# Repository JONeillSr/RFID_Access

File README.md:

# RFID Access Control

A door-access controller for ESP32 boards. Tap an enrolled RFID card to release a
door strike; everything else is denied. Built around a small set of reusable
libraries (WiFi provisioning, OLED display, splash screen) so the same codebase
drops onto multiple doors and multiple ESP32 variants with only a build-flag
change.

Status indication is on-device and over the network: a 0.96" OLED shows the
current state, an RGB LED gives an at-a-glance verdict, an active buzzer gives
audible feedback, and a built-in web server exposes status and over-the-air
firmware updates.

---

## Features

- **RFID access control** — Paxton P-series proximity reader (Clock & Data or
  Wiegand), enrolled-card allow-list stored in NVS (survives reboot and
  reflash). The reader can be mounted up to 100 m from the controller.
- **Door-side feedback** — drives the reader's own red/amber/green LED lines:
  amber "ready" when idle, green on grant, red on deny.
- **Fail-secure relay** — drives a door strike through a relay; the strike is
  de-energised (locked) whenever the controller is off or unpowered.
- **Exit button** — request-to-exit input (push-to-make to GND) releases the
  door from the secure side, no fob needed.
- **Door contact** — an optional magnetic contact on the frame reports a door
  **forced** open (opened with no grant, exit press or unlock window) or **held
  open** too long. Off until switched on, from the admin app or `/setup`. DevKit
  and S3 only; the C6 and C3 have no free input. *Bench-proven 2026-09-19 with a
  jumper standing in for the contact; not yet run with a reed switch fitted.*
- **Unlock schedule** — optionally holds the door unlocked during a configured
  time window on selected days (e.g. 08:00–17:00 weekdays), set from the web
  UI and stored in NVS. Time comes from NTP and the schedule **fails secure**:
  no time sync means the door stays locked.
- **Non-blocking throughout** — no `delay()` in the running system; relay
  release, result-screen revert, and LED timing all run off deadlines checked in
  `loop()`. FreeRTOS tasks separate RFID polling, access processing, and the web
  server.
- **OLED status display** — splash screen on boot, then an idle screen showing
  the mDNS hostname, IP address, and OTA hint; GRANTED / DENIED verdicts on tap.
- **Panel status LED** — green while the door is unlocked (plus red on denied,
  on boards with a free red channel; the C6's went to the exit button). Primary
  grant/deny indication is at the door, on the reader's own LEDs. Note the P50
  also beeps by itself on every token read and holds its amber LED as a
  power/ready indicator — both are built into the reader.
- **WiFi provisioning** — first boot raises a captive-portal AP with a network
  scanner; credentials are stored and reused on subsequent boots.
- **Changing WiFi without a site visit** — `/setup` moves a door to another
  network and **returns it to the working one if the new network does not come
  up**. For a network the door cannot see from where it is, the admin app arms
  the setup AP for its next restart, or holding the exit button at power-on
  opens the portal with no network at all.
- **mDNS** — reachable at `http://<hostname>.local` once connected.
- **Per-door identity** — one firmware image for every door. Each board derives a
  unique device ID from its MAC, so units never collide on the network, and
  hostname / door name / site name are set per unit on `/setup`.
- **OTA updates** — firmware can be flashed over the network via ElegantOTA at
  `/update`, or published once to the backend, which offers it to every paired
  door on that board running an **older** version. Going back is an explicit
  `--rollback`, never an accident of publishing.
- **Remote release** — an Operator can unlock a door for one relay hold from the
  admin app (**Doors → Release**), for letting in someone without a fob. Lands
  within seconds, is logged as *released remotely by &lt;name&gt;*, and is ignored if
  it reaches the door more than a minute late. Firmware 2.10.0 and later.
- **Remote restart** — an Admin can restart a door from the admin app
  (**Doors → Restart**). It waits until the strike is not mid-release, and lapses
  if the door does not check in within 15 minutes. Firmware 2.9.0 and later.
- **Remote logging** — live device log over the network at `/webserial` and via
  a telnet console (port 23), showing boot diagnostics and access events with no
  USB cable needed.
- **Multi-board** — one codebase targets the XIAO ESP32-C6, ESP32-C3, ESP32-S3,
  and the classic ESP32 DevKit, selected by a single build flag.

---

## Hardware

### Bill of materials

| Part | Notes |
|------|-------|
| ESP32 board | XIAO ESP32-C6 (primary), or ESP32-C3 / ESP32-S3 / classic ESP32 DevKit |
| Paxton reader | P-series 125 kHz proximity, e.g. P50 / 345-110-US; Clock & Data output |
| Pull-up resistors | 2× 10K, Data and Clock lines to a **clean 3.3 V rail** (not the ESP32's 3V3 pin — see wiring) |
| Exit button | any normally-open momentary switch (e.g. 30 mm arcade button) |
| Door contact *(optional)* | magnetic reed contact, **closed when the door is shut** |
| SSD1306 OLED | 0.96", I²C, address `0x3C` |
| Relay module | e.g. SONGLE SRD-05VDC-SL-C, active-LOW input with onboard driver + coil flyback diode |
| Door strike | DC, fail-secure (e.g. RCI L65) |
| Flyback diode | 1N4007 across the door strike — **required**, see Troubleshooting |
| RGB LED | common-cathode, with a current-limiting resistor per channel (220–330 Ω) |
| Active buzzer | |
| Power | 12 V supply; buck converters to 5 V and 3.3 V |

### Pin assignments

Pins are defined per board in `src/Pins.h`, with board-identity facts (I²C
defaults, capability flags, strapping-pin warnings) in `lib/BoardConfig/BoardConfig.h`.
Application code never references a raw GPIO — only the `PIN_*` names — so
retargeting a board is purely a build-environment change.

> **Verification status.** The **XIAO ESP32-C6** map is fully bench-verified
> in a working build: relay fail-secure confirmed clean through reboot with a
> meter, and Paxton P50 reads confirmed end-to-end (Clock & Data decode with
> LRC validation, reader LED control, exit button). The **classic ESP32
> DevKit** relay/buzzer/OLED/RGB pins are bench-verified from the RC522-era
> build; its Paxton pins reuse GPIOs proven there but haven't carried reader
> traffic yet. The **C3** and **S3** maps are plausible, strapping-pin-safe
> defaults that have **not** been hardware-verified. Before deploying to a C3
> or S3, confirm the relay pin shows no spurious pulse at boot (see
> Troubleshooting → "Verify the relay pin at boot"). Adjust `src/Pins.h` as
> needed.

**XIAO ESP32-C6:**

| Function | GPIO |
|----------|------|
| Paxton Data/D0 | D8 |
| Paxton Clock/D1 | D9 |
| Paxton Red / Green / Amber LED | D3 / D10 / D0 |
| Buzzer | D2 |
| Relay IN | GPIO1 |
| OLED SDA / SCL | 22 / 23 |
| Exit button | D6 (to GND) |
| Panel LED G | D7 (lights while door unlocked) |
| Panel LED R / B | not assigned — D6 was repurposed for the exit button; the reader's red LED shows "denied" at the door |

On the C6 every pad is now in use, so the panel LED is reduced to its green
channel only (dark idle, green while the door is unlocked). Full at-the-door
feedback — amber ready, green granted, red denied — comes from the Paxton
reader's own LEDs.

**Classic ESP32 DevKit:**

| Function | GPIO |
|----------|------|
| Paxton Data/D0 | 19 |
| Paxton Clock/D1 | 18 |
| Paxton Red / Green / Amber LED | 17 / 23 / 4 |
| Buzzer | 13 |
| Relay IN | 14 |
| OLED SDA / SCL | 21 / 22 |
| Exit button | 32 (to GND) |
| Door contact | 33 (to GND) |
| LED R / G / B | 25 / 26 / 27 |

### Paxton reader wiring

The reader connects with the same terminal roles as on a Paxton Net2 ACU —
if migrating from a Net2, each reader wire moves from the Net2 reader-port
terminal to the matching ESP32 connection.

Paxton P50 (345-110-US) wire colors — bench-verified on this unit by
grounding the LED lines and watching the data lines during a tap. Note the
loom differs from older Paxton manuals (no brown wire; Red LED is purple
here, not brown):

| Wire color | Function | Connection (XIAO C6) |
|-----------|----------|----------------------|
| Red | 12V | PSU + |
| Black | 0V | PSU − / ESP32 GND (plus cable screen) |
| Yellow | Data/D0 | D8 (10K pull-up to 3V3) |
| Blue | Clock/D1 | D9 (10K pull-up to 3V3) |
| Purple | Red LED | D3 |
| Orange | Amber LED | D0 |
| Green | Green LED | D10 |
| White | Media detect (reader output; unconfirmed) | not connected |

Yellow/blue both carry the transmission, so a meter can't tell Data from
Clock — wire as above and tap a token: card numbers reading correctly
confirms it, while a rising decode-error counter on `/status` with no reads
means the pair is swapped (swap the two wires and retest).

> **Warning:** Paxton colors do NOT follow the common Wiegand convention.
> On most third-party readers green = D0 and white = D1; on a Paxton, green
> is an LED line — the data pair is **yellow and blue**. Grounding an LED
> wire lights that LED; the data/clock wires blip low during a card read.

- **12V / 0V** — from the 12 V supply. The reader's 0V must be commoned with
  the ESP32's ground, or the data lines have no reference.
- **Data/D0 and Clock/D1** — open-collector outputs from the reader. Fit a
  **10K pull-up from each line to a clean 3.3 V source** (never to 5 V or
  12 V — ESP32 pins are not 5 V tolerant). Verify with a meter that both lines
  idle at ~3.3 V before connecting to the GPIOs.

  > **Use a stiff 3.3 V rail for the pull-ups, not the ESP32 module's own
  > 3V3 pin.** Bench-proven the hard way: pull-ups referenced to the ESP32's
  > 3V3 pin produced randomly duplicated clock bits (the module's rail
  > bounces with WiFi transmit bursts, so slow rising edges re-cross the
  > input threshold). Moving the pull-ups to a dedicated 3.3 V buck output
  > fixed it completely. The pull-up rail must share ground with the ESP32,
  > power up/down with it, and measure ≤ ~3.5 V.
- **Red / Amber / Green LED** — active-low control inputs; the firmware drives
  them open-drain (sinks to light, floats to release), the same way the Net2
  does. Measure each LED line's idle voltage first: if one floats above
  3.3 V, sink it through a small NPN transistor or N-MOSFET instead of the
  GPIO directly.
- **Media Detect** — unused; leave disconnected.

Cable: Cat5 or Belden 8723 class, up to **100 m**. Past 25 m, double up the
12V and 0V cores to limit voltage drop (Paxton's own guidance for Net2 runs).

### Exit button, door contact and unlock schedule

**Exit button:** any push-to-make button wired between `PIN_EXIT_BTN` and
GND (internal pull-up; active low). Pressing it releases the door for the
normal relay hold time — no fob required. Wiring is identical to the Net2's
Exit/0V terminal pair.

**Door contact** *(new in 2.8.0)*: a magnetic reed contact on the frame,
wired between `PIN_DOOR_CONTACT` and GND (internal pull-up) — GPIO 33 on the
DevKit, 17 on the S3. The C6 and C3 have no free input. Then switch it on: for a
paired door, in the admin app under **Doors → edit → Door contact fitted**
(`/setup` shows it read-only there, as it does the reader format); otherwise on
the door's own `/setup`. It is off by default because an unwired
input reads as an open door.

- Use a contact that is **closed when the door is shut**. A cut wire then reads
  as open and raises an alert, instead of reading "closed" forever. (For the
  other kind, set `DOOR_CONTACT_OPEN_LEVEL` to `LOW` in `src/Pins.h`.)
- **Door forced** is reported when the door opens with no grant or exit press in
  the last relay hold plus 2 s, and no unlock window open.
- **Door held open** is reported when it stays open longer than the limit on
  `/setup` (default 60 s) after the last release ended, and again with the total
  time once it closes.
- **If the door opens from inside without the exit button** (a lever handle),
  every such exit reads as forced. Wire a request-to-exit switch or motion
  sensor to the exit button input before relying on the forced alert.
- Forced openings appear on the admin dashboard. See Phase 6 in `ROADMAP.md`
  for what is verified so far.

**Unlock schedule:** configured on the `/config` page — enable, start/end
time, and days of week; an end time before the start time makes an overnight
window. While active, the relay is held energised, the reader LED shows
green, and the OLED idle screen reads `** DOOR UNLOCKED **`. The clock comes
from NTP (synced on WiFi connect; timezone is `TZ_INFO` in `src/main.cpp`,
default US Eastern). Fail-secure rule: if the clock has never synced since
boot, the schedule stays inactive and the door stays locked. Note that a
fail-secure strike is energised for the whole window — check your strike's
duty-cycle rating, or use a maglock/continuous-duty strike for long windows.

The reader outputs **Clock & Data** (Paxton's native format) by default, which
is what the firmware expects. If the reader has been switched to Wiegand with a
Paxton configuration card — or a third-party Wiegand reader is fitted — set
**Reader format → Wiegand** and **reboot**. Set it in the **admin app** (Doors →
edit → Reader format) for a paired door; `/setup` shows it read-only there, the
same as the roster and schedule. An unpaired door sets it on `/setup` (the format decides which
interrupts attach, so it is applied at boot; `/setup` shows "reboot pending"
until then, and `/status` shows the running format). Wiegand D0 goes to the
Data terminal and D1 to the Clock terminal. Only Paxton on Clock & Data is
verified so far — qualify any other reader with
[`docs/reader-qualification.md`](docs/reader-qualification.md) before promising it.

### Relay and door-strike wiring

The relay switches +12 V to the door strike's positive terminal (high-side
switching); the strike's other lead returns to ground. **A 1N4007 flyback diode
must be fitted directly across the door strike's two terminals**, banded end
(cathode) toward the strike's positive (relay-NO) lead. Without it, the strike's
inductive kick on relay release couples into the shared supply and can wedge the
RFID reader. The relay module's own onboard diode protects only the relay coil,
not the strike — see Troubleshooting for the full story.

---

## Software setup

### Prerequisites

- [PlatformIO](https://platformio.org/) (VS Code extension or CLI)
- The **pioarduino** fork of the ESP32 platform — required for current
  ESP32-C6 support. This is pinned in `platformio.ini`, so PlatformIO fetches it
  automatically; no manual install needed.
- Python, for the tools in `tools/` and for the git hooks below.

### Enable the git hooks (once per clone)

```bash
git config core.hooksPath .githooks
```

Git does not use tracked hooks until you point it at them, and nothing warns you
— so a fresh clone silently has no protection until this is run.

The hooks refuse to commit anything that looks like a **card number**, in file
content and in commit messages alike. Fob numbers are credentials: anyone holding
one can clone a working card. The `.gitignore` rules already keep `seed.json` and
`*-fobs.json` out, but they protect known *files* — a number pasted into source
as a placeholder walks straight past them, which is exactly how one reached a
commit here. Run `python tools/check_card_numbers.py --all` to scan the whole
tree by hand.

### Build environments

Each board has its own environment in `platformio.ini`. The default is the C6.

| Environment | Board | Build flag |
|-------------|-------|------------|
| `seeed_xiao_esp32c6` | XIAO ESP32-C6 (default) | `BOARD_XIAO_ESP32C6` |
| `esp32c3` | ESP32-C3 DevKitM | `BOARD_ESP32C3` |
| `esp32s3` | ESP32-S3 DevKitC | `BOARD_ESP32S3` |
| `esp32dev` | classic ESP32 (WROOM) | `BOARD_ESP32DEV` |

All environments use the `min_spiffs` partition scheme to keep two OTA app slots
on 4 MB flash. ElegantOTA is forced into sync-WebServer mode via
`-D ELEGANTOTA_USE_ASYNC_WEBSERVER=0`.

### Build and flash

Build for the default board (C6):

```
pio run
```

Build for a specific board:

```
pio run -e esp32dev
```

Flash over USB:

```
pio run -e seeed_xiao_esp32c6 -t upload
```

Serial monitor (115200 baud):

```
pio device monitor
```

> **Note on the ESP32-C6 and serial:** the C6 uses native USB CDC, which drops on
> reboot and re-enumerates too slowly to catch boot messages. Diagnostics on the
> C6 therefore go to the OLED and the web `/status` page, not the serial monitor.
> The classic ESP32 DevKit uses an external USB-UART chip whose serial **survives
> reboot**, so on that board the monitor is fully usable for boot debugging.

---

## First-time use

1. **Flash** the firmware for your board.
2. **Provision WiFi.** On first boot (no stored credentials), the device raises a
   WiFi access point named `RFID-Setup`. Join it from a phone or laptop; a
   captive portal opens automatically (or browse to `http://192.168.4.1`). Pick
   your network, enter the password, and save. The device reboots and connects.

   The same portal appears if the door boots while its saved network is down —
   after a power cut, for example. **It does not need re-entering:** from 2.7.4
   the door keeps retrying the saved network and returns on its own within a
   couple of minutes of the network coming back. Earlier firmware stayed in the portal
   until someone rejoined it.
3. **Find the device.** Once connected, the OLED shows the hostname, the IP
   address, and the OTA hint. Out of the box the hostname is this board's unique
   device ID (`rfid-a1b2c3.local`) — read it off the OLED and browse to it, or
   use the IP. Give it a friendlier name on `/setup`.
4. **Enrol cards** via the web interface, then tap to test: a granted card
   energises the relay (green LED, door unlocks); an unknown card is denied (red
   LED).

### Web endpoints and remote logging

The web server, OTA, status page, and remote log are owned by the reusable
`WebService` module (`lib/WebService/`), which creates the server, serves the
common admin pages, and lets the project register its own routes and inject
app-specific status fields.

| Path | Purpose |
|------|---------|
| `/` | main web UI (card enrolment) |
| `/config` | fob management + unlock-schedule configuration |
| `/setup` | device settings: splash hold, mDNS hostname, door name, site name, **WiFi network** (try-then-revert), **reader format**, **relay hold and result-screen hold**, door contact and held-open limit, **backend host**, cloud pairing code; plus a **Reboot device** button |
| `/api/schedule` | GET current schedule/state, POST to update |
| `/api/add` `/api/rename` `/api/remove` | fob management (POST, JSON) |
| `/api/list` `/api/taps` | roster and recent taps (GET, JSON) |
| `/status` | live status page: device ID, door and site, WiFi IP, **`Signal:`** strength in dBm with a rating, channel and access point (BSSID), mDNS name, uptime, **heap** (free / min since boot / largest block), OLED, **`Reader:`** running line format (and any pending change), time **and how long since NTP**, schedule, **`Relay:`** hold per grant and result-screen hold, **`Contact:`** door state, **`WiFi:`** network and any move in progress, enrolled count, **`Backend:`** host, cloud sync state, **`Retry:`** backoff when not on the normal poll, **`Remote:`** how a remote release will arrive (polling the feed every 3 s, or next sync only and why), event spool, last tap |

The heap line is worth reading properly, because two of its three numbers have
already been the difference between a diagnosis and a guess:

```
Heap:  132 KB free, min 71 KB since boot, largest block 91 KB
```

**Free heap is the least useful of the three.** It describes the instant you
looked. `min since boot` survives a spike that has passed, and `largest block` is
what large allocations actually compete for — a TLS handshake needs ~45 KB
*contiguous*, so plenty free in small pieces will still fail. A roster-write
failure was once diagnosed from exactly this line while free heap looked
entirely healthy.

From 2.12.3 a note under the line says when the **release feed** connection is
open and roughly how much it holds (about 55 KB). The feed keeps a TLS session
open between syncs to check for remote releases every 3 seconds, and closes it
before each sync, so a reading taken while it is open understates what a sync
gets. Fragmentation shows as a small largest block with the feed **closed**. The
copy the admin app shows (**Doors → Status**) is taken during a sync, with the
feed closed, so it is the one to judge by.

#### Write endpoints go read-only once a door is paired

`/api/add`, `/api/rename`, `/api/remove` and `POST /api/schedule` answer **409**
while a door is centrally managed, and `/config` shows a banner saying so. The
read endpoints are untouched, so a door still explains itself locally even with
the network gone.

A controller that can enrol its own fobs while offline is an attack surface:
anyone reaching one door's page could add themselves, and the central database
would not know until it silently overwrote the entry on the next sync. It also
leaves the roster with exactly one writer, so local and central cannot drift.

The accepted cost is that a fob cannot be enrolled during a WAN outage — doors
keep working from their cached rosters, but the fob list is frozen until the link
returns. **Unpaired units keep full local control**, so a bench unit behaves
exactly as it always did, and unpairing on `/setup` hands control back
immediately without a reboot.

#### The backend is runtime configuration

The host a door reports to is stored in NVS and set on `/setup`, not compiled in.
`CLOUD_HOST_DEFAULT` in `src/main.cpp` is only the value a door uses until told
otherwise, so existing units need no migration.

One image therefore serves every deployment. **Changing the host unpairs the
door** — a device key is issued by the backend that minted it and is meaningless
to another — so enter a pairing code from the new backend in the same submission.
The host is applied first precisely so that works in one step.
| `/footer.js` | shared footer the WebService module injects into every page |
| `/update` | ElegantOTA firmware upload |
| `/webserial` | live device log (self-refreshing); shows boot diagnostics and access events |

A **telnet log console** is also available on port 23 (`telnet <host>.local`),
showing the same log stream as `/webserial`. Both are fed by `webService.log()`
calls placed at key events (reader-interface boot line, WiFi connect, each
access grant or deny). Note the telnet console is plaintext and unauthenticated — fine for a
trusted LAN or bench, but consider disabling it on field units exposed to
untrusted networks.

### Per-door deployment

**One firmware image serves every door.** Identity comes from hardware and NVS,
not from a build flag, so nothing needs recompiling per unit.

Each board derives a permanent **device ID** from its MAC — `rfid-a1b2c3` — which
is unique out of the box, survives reflashing and an NVS erase, and is what a
backend keys on. Until you set a hostname, that device ID *is* the mDNS name, so
**two units can never collide on the network by default**.

On `/setup` you can give each unit friendlier labels:

| Field | Purpose |
|-------|---------|
| mDNS hostname | Network name, e.g. `rfid-front` → `http://rfid-front.local` |
| Door name | Human label for reports, e.g. "Front Door" |
| Site name | Groups doors sharing a building, e.g. "Main Shop" |
| Device ID | Read-only; the fixed MAC-derived identity |

Door and site names apply immediately. A changed **hostname takes effect after a
reboot**, since the mDNS responder is started at boot — and `/setup` carries a
**Reboot device** button for exactly that, so renaming a door doesn't mean walking
to it. The reboot endpoint is POST-only, so no link prefetch or crawler can
restart a unit. The lock is fail-secure, so a reboot leaves the door locked.

Hostnames are sanitised before use — lowercased, restricted to `a-z0-9-`, spaces
and underscores folded to `-`. Typing "Front Door" yields `front-door` rather than
an invalid label that would make the unit silently unresolvable.

Identity flows from `DeviceIdentity` into `wifiMgr.setHostname()`, the OLED idle
screen, and the `/status` page, which now leads with device ID, door, and site so
you can tell units apart at a glance.

---

## Project structure

```
lib/                    reusable, application-agnostic libraries
  BoardConfig/          per-board identity + capability flags (compile-time)
  Display/              SSD1306 OLED helpers (caller owns the I2C bus)
  SplashScreen/         boot splash
  WiFiManager/          provisioning, STA lifecycle, mDNS, NTP time sync
  WebService/           owns the web server: /status, /update (OTA),
                        /webserial, telnet log console, shared page footer,
                        optional /setup; projects add routes
  DeviceSettings/       NVS settings store (WebService dependency)
  DeviceIdentity/       MAC-derived device ID, mDNS hostname, door/site labels
  Roster/               LittleFS credential store: hash-keyed, CRC-checked,
                        atomic save, atomic wholesale replace for cloud sync
  EventLog/             durable append-only event spool held until the backend
                        acknowledges it (taps, exit, schedule, boot, config,
                        firmware, door forced/held)
  DoorContact/          forced-open and held-open decisions from a reed contact.
                        Pure logic: the caller reads the pin and supplies the
                        release state, so the rules sit in one readable place
  CloudSync/            backend sync client + OTA: uploads spooled events,
                        applies the roster/config the server returns, and takes
                        firmware updates. Runs on its own task and is NEVER in
                        the access decision path. Embeds its own TLS trust
                        anchors (certs/ + RootCerts.h) -- an ESP32 has no system
                        trust store.
  AccessControl/        access decision + recent-tap log (storage lives in Roster)
  Events/               app event types + queue (card-tap, exit-request)
  PaxtonReader/         Clock & Data / Wiegand reader driver + reader LEDs
  UnlockSchedule/       NVS-backed timed-unlock window (fails secure w/o NTP)
  WebHandlers/          project-specific web UI routes
src/                    project-specific code
  main.cpp              wiring, tasks, screens, relay/LED/buzzer logic
  Pins.h                per-board peripheral pin map
  JTLogoBitmap.h        splash bitmap
tools/                  operational scripts
  backup-doors.ps1      snapshot a door's fobs + schedule before a reflash
  check_partitions.py   validate partitions_rfid.csv (incl. NVS preservation)
  check_roster_logic.py exercise Roster's ordering/lookup algorithms
  gen_certs.py          regenerate lib/CloudSync/RootCerts.h from the PEMs in
                        lib/CloudSync/certs/ (see that header for how to
                        re-extract and verify an anchor before trusting it)
  wrap_standalone.py    regenerate docs/board-bringup.html from the published
                        version (adds the doctype/head a hosted page supplies)
docs/                   printable references
  board-bringup.html    one-page field guide for adding a new board type: the
                        gates, the verification at each one, and where mistakes
                        stop being recoverable. Open it directly and print.
cloud/                  Azure backend (TypeScript, deployed separately)
  shared/types.ts       contract shared by the API and the admin web app
  api/                  Azure Functions: device sync/enroll + the admin API
  web/                  admin web app (Preact + Vite) on Static Web Apps
  infra/                Bicep: storage, tables, Function App, SWA, observability
```

Each of those three has its own README covering deployment and the decisions
behind it; the admin app is live at `https://access.jtcustomtrailers.com`.

`ROADMAP.md` tracks the multi-door / cloud programme: what is built, what is
next, and — more usefully — why each decision went the way it did.

The split is deliberate: `lib/` holds code reusable across projects and visible
to other libraries; `src/` holds this project's specifics. Two complementary
networking modules divide the work cleanly: **WiFiManager** owns *connectivity*
(provisioning, STA lifecycle, reconnect, mDNS), while **WebService** owns the
*web/admin surface* (the long-lived server, OTA, status, remote logging).
Neither reaches into the other; a project composes both.

---

## Design principles

- **Non-blocking only.** `delay()` is forbidden in the running system; all timing
  uses deadlines checked in `loop()` or `vTaskDelay` inside tasks.
- **Canonical storage, convert at the edges.** State is stored in base units and
  formatted only at the display/input boundary.
- **Modular and board-agnostic.** Reusable modules in `lib/`, project specifics in
  `src/`, board differences behind a single build flag.
- **Fail-secure.** The lock defaults to secured; the relay is brought to a safe
  state before anything else at boot.

---

## Troubleshooting

### Granted tap locks up the reader (no further cards read until power-cycle)

**Cause:** inductive flyback. On a granted tap the relay energises the door
strike; when the relay releases, the strike's collapsing magnetic field produces
a voltage spike. On a shared supply that spike couples into the RFID reader and
wedges it. The tell is that the lockup happens on relay **release**, and only on
granted taps (denied taps never fire the relay).

**Fix:** fit a 1N4007 flyback diode **directly across the door strike's two
terminals**, banded end (cathode) toward the strike's positive (relay-NO) lead.
Mount it at the strike, not back at the board, so the spike is clamped at its
source. The relay module's onboard diode only protects the relay coil — the
external strike is a separate inductor and needs its own clamp.

This applies to **DC** strikes. An AC strike needs an RC snubber or MOV instead;
a diode across an AC coil will conduct every half-cycle and fail.

### Reading the reader counters on /status

`Reader: Paxton Clock&Data, E edge(s), N error(s), R repaired` is a built-in
diagnostic ladder (a tap should add ~80-100 edges):

- **Edges don't move on a tap** → no signal reaches the GPIOs at all. The
  reader beeping proves nothing — its sounder fires on every read, powered or
  not by your wiring. Check, in order: reader 0V **commoned with the ESP32
  ground** (without a shared reference the open-collector lines never swing);
  the pull-ups (both lines should idle at ~3.3 V at the ESP32); the wires on
  the right pads. Tip: the exit button test — press it and watch for the
  reader's green LED — proves ground + LED drive in one shot.
- **Edges jump, errors increment, never a card number** → bits arrive but
  won't parse. Every failed frame is logged with its raw bits
  (`[paxton] undecodable frame: 0001101...` at `/webserial`), which makes
  the cause readable: wrong line format (reader switched to Wiegand → set
  **Reader format** on `/setup` and reboot), swapped Data/Clock, or all-same
  bits (the data pin is on the wrong wire — Media Detect also dips during a
  read and fools a multimeter).
- **Reads work but `repaired` keeps climbing** → line quality is marginal.
  The driver absorbs one duplicated bit per frame (ISR glitch filter +
  parity/LRC-gated single-bit repair), but fix the electricals: the classic
  cause is pull-ups referenced to the ESP32 module's own 3V3 pin, which
  bounces with WiFi bursts — move them to a stiff 3.3 V rail (bench-proven
  here). On long runs also drop to 4.7K and pair each signal with 0V, not
  with each other.

### Reader LEDs don't respond (or an LED is dimly on)

The LED lines are active-low and driven open-drain. A line that floats above
3.3 V at idle exceeds what the GPIO can safely sink directly — buffer it with a
small NPN transistor or N-MOSFET (gate/base from the GPIO, drain/collector to
the LED line, source/emitter to ground) and the firmware logic is unchanged.

### OLED stays dark / not found

On the ESP32-C6, `Wire1` (the second I²C peripheral) is broken
([arduino-esp32 #10685](https://github.com/espressif/arduino-esp32/issues/10685));
all I²C devices must share the single `Wire` bus on GPIO 22/23. Separately, the
Adafruit SSD1306 `begin()` defaults to re-initialising the I²C peripheral with no
pin arguments, which overrides explicitly configured pins. The Display library
works around this by passing `periphBegin=false` and adding a short settle delay
before `begin()`. If you port the display code elsewhere, carry those workarounds
with it.

### Can't see boot messages on the C6

Expected. The C6's native USB CDC serial drops on reboot and reconnects too
slowly to catch boot output. Use the OLED and the `/status` web page for
diagnostics, or build for the classic ESP32 DevKit (external USB-UART) when you
need to watch boot. This is a hardware characteristic, not a bug.

### Verify the relay pin at boot (non-C6 boards)

The relay pin must not glitch high during boot, or a fail-secure lock could
momentarily release at power-up. The C6's relay pin (GPIO1) is bench-verified
clean. For any other board, before connecting the strike: flash the firmware with
the strike disconnected, put a meter on the relay output, and power-cycle several
times watching for any spurious pulse. If you see one, move the relay to a
different non-strapping GPIO in `src/Pins.h` and retest. Only connect the strike
once the pin is proven quiet.

### `.local` address doesn't resolve

mDNS `.local` resolution works from most macOS, iOS, Linux, and modern Windows
clients, but some Android devices and older Windows versions can't resolve it.
Use the IP address shown on the OLED as a fallback. The IP is always displayed
alongside the hostname for this reason.

### Build fails: a library can't find a header

PlatformIO compiles each `lib/` library in isolation — a library can see other
libraries but **cannot** see `src/`. If a library include fails, the header it
wants is probably in `src/`. Move shared headers into their own `lib/` module
(as is done for `Events/`); keep project-only headers in `src/`.

---

## License

Released under the MIT License. See [`LICENSE`](LICENSE) for details.

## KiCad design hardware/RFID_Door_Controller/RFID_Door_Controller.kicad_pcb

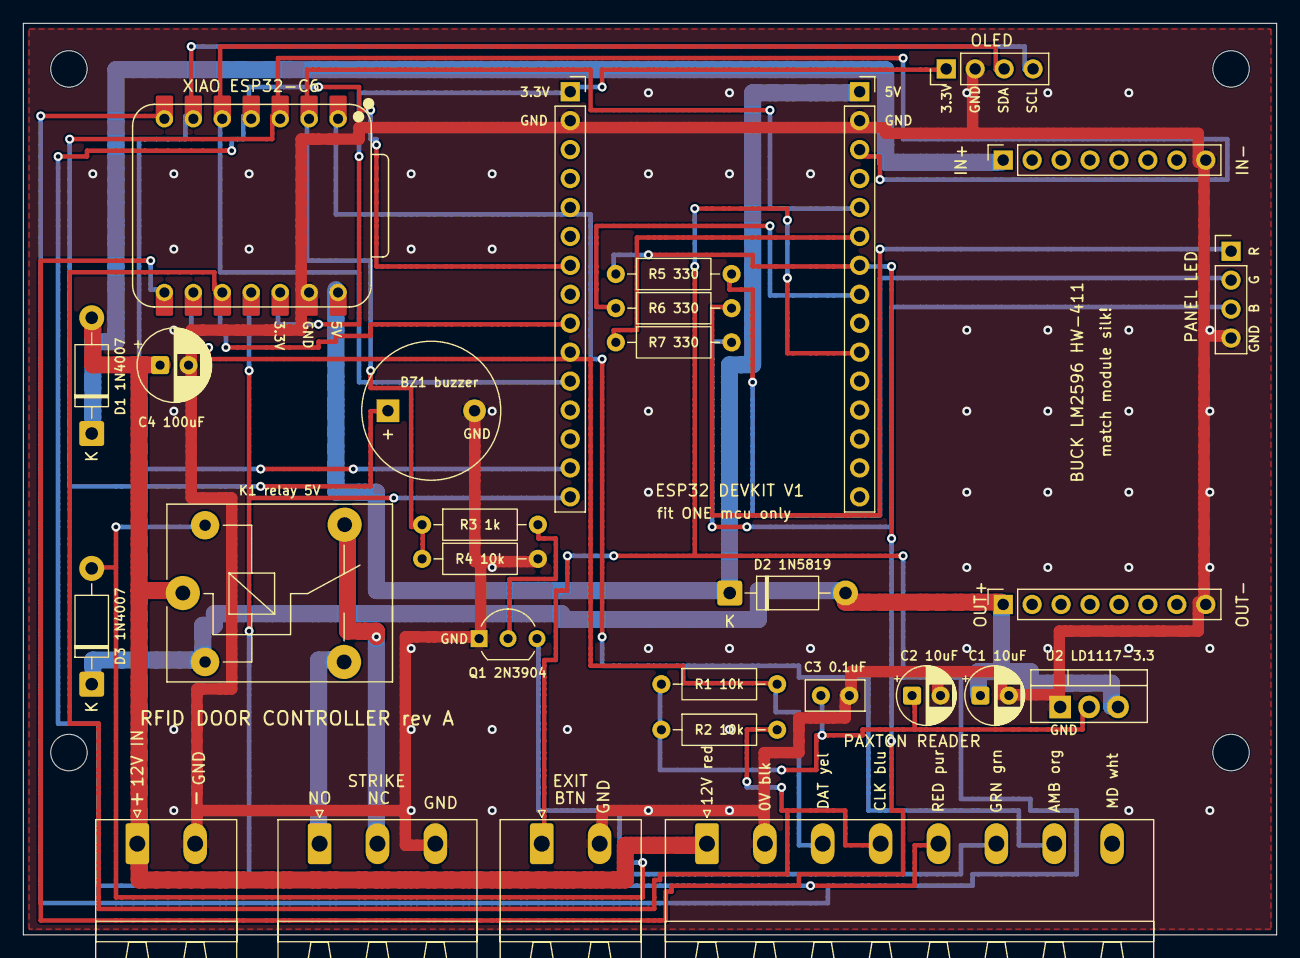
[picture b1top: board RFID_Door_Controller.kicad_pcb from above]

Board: 2 copper layers, 110.0 x 80.0 mm, 33 parts (0 on the bottom side), 27 nets.

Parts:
BZ1: Buzzer_12x9.5RM7.6
C1, C2: 10u; CP_Radial_D5.0mm_P2.50mm
C3: 100n; C_Disc_D5.0mm_W2.5mm_P2.50mm
C4: 100u; CP_Radial_D6.3mm_P2.50mm
D1, D3: 1N4007; D_DO-41_SOD81_P10.16mm_Horizontal
D2: 1N5819; D_DO-41_SOD81_P10.16mm_Horizontal
H1, H2, H3, H4: MountingHole_3.2mm_M3
J1, J5: PhoenixContact_MSTBA_2,5_2-G-5,08_1x02_P5.08mm_Ho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; PhoenixContact_MSTBA_2,5_2-G-5,08_1x02_P5.08mm_Horizontal
J2, J10: PinSocket_1x08_P2.54mm_Vertical
J3: PhoenixContact_MSTBA_2,5_8-G-5,08_1x08_P5.08mm_Ho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; PhoenixContact_MSTBA_2,5_8-G-5,08_1x08_P5.08mm_Horizontal
J4: PhoenixContact_MSTBA_2,5_3-G-5,08_1x03_P5.08mm_Ho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; PhoenixContact_MSTBA_2,5_3-G-5,08_1x03_P5.08mm_Horizontal
J6, J7: PinHeader_1x04_P2.54mm_Vertical
J8, J9: PinSocket_1x15_P2.54mm_Vertical
K1: SRD-05VDC-SL-C; Relay_SPDT_SANYOU_SRD_Series_Form_C
Q1: 2N3904; TO-92_Inline_Wide
R1, R2, R4: 10k; R_Axial_DIN0207_L6.3mm_D2.5mm_P10.16mm_Horizontal
R3: 1k; R_Axial_DIN0207_L6.3mm_D2.5mm_P10.16mm_Horizontal
R5, R6, R7: 330; R_Axial_DIN0207_L6.3mm_D2.5mm_P10.16mm_Horizontal
U1: XIAO-ESP32-C6-DIP
U2: LD1117V33; TO-220-3_Vertical

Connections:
3V3_MCU: J6.1, J8.1, U1.12
3V3_PU: C2.1, C3.1, R1.1, R2.1, U2.2
5V: C1.1, D2.2, D3.1, J10.1, K1.2, U2.3
5V_MCU: D2.1, J9.1, U1.14
12V_PROT: D1.1, J2.1
12V_RAW: C4.1, D1.2, J1.1, J3.1, K1.1
AMBER_LED: J3.7, J8.5, U1.1
BUZZER: BZ1.1, J9.3, U1.3
CLOCK: J3.4, J8.9, R2.2, U1.10
COIL_SW: D3.2, K1.5, Q1.3
DATA: J3.3, J8.10, R1.2, U1.9
EXIT_BTN: J5.1, J9.10, U1.7
GND: BZ1.2, C1.2, C2.2, C3.2, C4.2, J1.2, J2.8, J3.2, J4.3, J5.2, J6.2, J7.4, J8.2, J9.2, J10.8, Q1.1, R4.2, U1.13, U2.1
GREEN_LED: J3.6, J8.15, U1.11
PANEL_B: J9.6, R7.1
PANEL_B_J: J7.3, R7.2
PANEL_G: J9.7, R5.1, U1.8
PANEL_G_J: J7.2, R5.2
PANEL_R: J9.8, R6.1
PANEL_R_J: J7.1, R6.2
Q1_B: Q1.2, R3.2
RED_LED: J3.5, J8.7, U1.4
RELAY_CTL: J9.5, R3.1, R4.1, U1.2
SCL: J6.4, J8.14, U1.6
SDA: J6.3, J8.11, U1.5
STRIKE_NC: J4.2, K1.4
STRIKE_NO: J4.1, K1.3
